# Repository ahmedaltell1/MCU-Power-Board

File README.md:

# Custom MSP430 Embedded Systems PCB

## Overview

This project is a custom-designed embedded systems PCB developed in KiCad. The board integrates a regulated power delivery stage, an MSP430 microcontroller subsystem, sensor interfaces, switch inputs, and IoT communication support into a single embedded hardware platform.

The system was designed to demonstrate practical embedded hardware development, PCB design workflow, sensor integration, power regulation, and hardware/software interfacing.

Additionally, the project incorporates an ultrasonic water-level detection system capable of monitoring liquid levels through embedded sensing and real-time signal interfacing.

---

## Features

- Custom PCB designed in KiCad
- MSP430 microcontroller integration
- Regulated power delivery subsystem
- Ultrasonic water-level detection
- Sensor interface circuitry
- Embedded switch inputs
- IoT communication module support
- Modular embedded hardware architecture
- Manufacturable PCB layout and fabrication files

---

## Hardware Components

- MSP430 microcontroller
- Voltage regulation circuitry
- Ultrasonic sensor interface
- IoT communication module
- GPIO switch interfaces
- Passive filtering and protection components

---

## Design Tools

- KiCad
- LTspice
- Embedded hardware debugging tools

---

## Repository Structure

```text
custom-msp430-pcb/
├── schematics/       # Schematic source and exported PDFs
├── pcb/              # PCB layout files and renders
├── gerbers/          # Manufacturing Gerber files

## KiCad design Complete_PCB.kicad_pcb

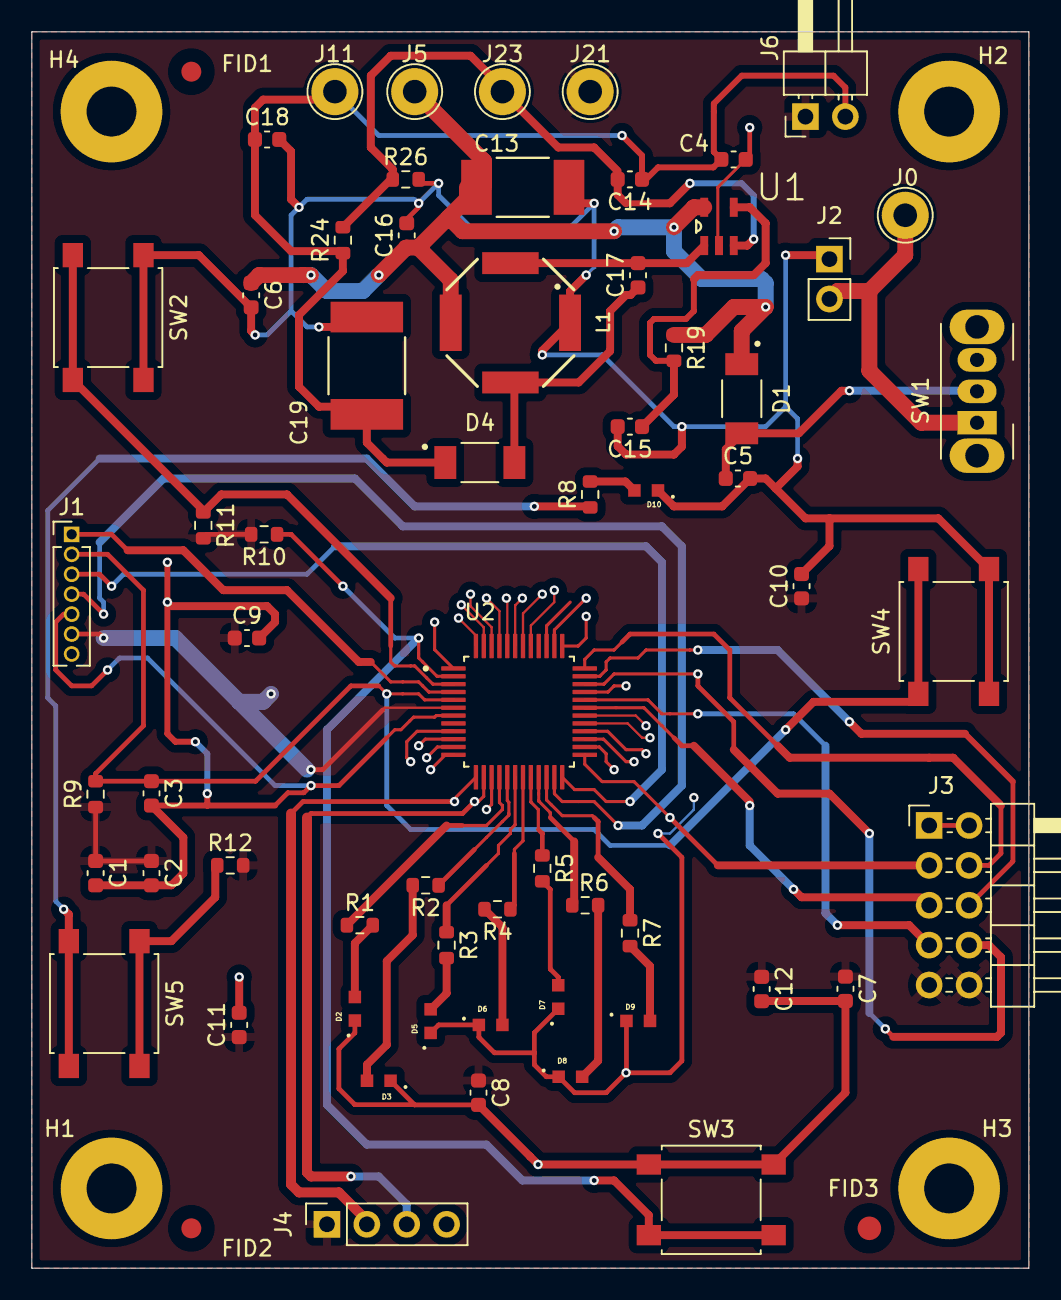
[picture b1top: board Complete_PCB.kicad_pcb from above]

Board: 2 copper layers, 63.5 x 78.7 mm, 69 parts (0 on the bottom side), 41 nets.

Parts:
C1: 0.1uF; C_0603_1608Metric
C2, C4, C5, C6, C7, C8, C9, C10, C11, C12, C18: 10uF; C_0603_1608Metric
C3: 1nF; C_0603_1608Metric
C13: 22uF; CAP_595D-C_VSS
C14, C15: 470pF; C_0603_1608Metric
C16, C17: 1uF; C_0603_1608Metric
C19: 100uF; CAP_594D-D_VSS
D1, D4: PMEG3050EP_115; DIO_PMEG3050EP_115
D2, D3, D5, D6, D7, D8, D9, D10: LTST-C190GKT; LEDM1608X80
FID1, FID2, FID3: Fiducial; Fiducial_1.5mm_Mask3mm
H1, H2, H3, H4: MountingHole_Pad; MountingHole_3.2mm_M3_Pad_TopOnly
J0, J5, J11, J21, J23: TestPoint; TestPoint_THTPad_D3.0mm_Drill1.5mm
J1: Conn_01x07_Pin; PinHeader_1x07_P1.27mm_Vertical
J2: Conn_01x02; PinSocket_1x02_P2.54mm_Vertical
J3: Conn_02x05_Odd_Even; PinHeader_2x05_P2.54mm_Horizontal
J4: Conn_01x04_Socket; PinSocket_1x04_P2.54mm_Vertical
J6: Conn_01x02_Pin; PinHeader_1x02_P2.54mm_Horizontal
L1: WE-TDC_8038
R1, R2, R3, R4, R5, R6, R7, R8: 1k; R_0603_1608Metric
R9, R10, R11, R12, R19: 10k; R_0603_1608Metric
R24: 20k; R_0603_1608Metric
R26: 12k; R_0603_1608Metric
SW1: SW_SPST; SW_Slide_SPDT_Angled_CK_OS102011MA1Q
SW2, SW3, SW4, SW5: SW_DIP_x01; SW_SPST_B3S-1000
U1: LT1935ES5TRMPBF; SOT95P280X100-5N
U2: MSP430FR2355TPT; QFP50P900X900X160-48N

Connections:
/PWR5A: C6.1, C13.1, C16.1, D1.K, J5.1, L1.3, R19.1, U1.5 (VIN)
/RAW_BAT: J0.1, J2.2, SW1.1 (A)
/Sheet2/CPU_RXDA: J3.7, U2.32 (P1.6/UCA0RXD/UCA0SOMI/TB0.1/TDI/TCLK/OA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)
/Sheet2/CPU_TXDA: J3.5, U2.31 (P1.7/UCA0TXD/UCA0SIMO/TB0.2/TDO/OA1+/A7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)
/Sheet2/Echo: J4.3, U2.14 (P4.5/UCB1CLK)
/Sheet2/IOT_BOOTA: J3.4, U2.36 (P3.6/OA3-)
/Sheet2/IOT_EN: J3.3, U2.25 (P4.1/UCA1CLK)
/Sheet2/IOT_LINK: J3.6, U2.35 (P3.7/OA3+)
/Sheet2/IOT_RUN: J3.8, U2.34 (P1.4/UCA0STE/TCK/A4)
/Sheet2/LED7: R7.1, U2.22 (P6.0/TB3.1)
/Sheet2/RST: C3.1, J1.2, R9.2, SW4.2, U2.5 (~RST/NMI/SBWTDIO)
/Sheet2/RXD: J1.3, U2.24 (P4.2/UCA1RXD/UCA1SOMI/~UCA1RXD)
/Sheet2/SW2: R11.1, SW2.2, U2.3 (P1.0/UCB0STE/SMCLK/COMP0.0/A0/VEREF+)
/Sheet2/SW3: R10.1, SW3.2, U2.2 (P1.1/UCB0CLK/ACLK/OA0O/COMP0.1/A1)
/Sheet2/TEST: J1.1, U2.4 (TEST/SBWTCK)
/Sheet2/TXD: J1.4, U2.23 (P4.3/UCA1TXD/UCA1SIMO/~UCA1TXD)
/Sheet2/Trig: J4.2, U2.13 (P4.6/UCB1SIMO/UCB1SDA)
GND: C1.2, C2.2, C3.2, C4.2, C5.2, C6.2, C7.2, C8.2, C9.2, C10.2, C11.2, C12.2, C13.2, C15.2, C16.2, C18.2, C19.2, D2.C, D3.C, D5.C, D6.C, D7.C, D8.C, D9.C, D10.C, J1.5, J2.1, J3.1, J3.2, J4.4, L1.1, R26.2, SW2.1, SW3.1, SW4.1, U1.2 (GND), U2.7 (DVSS)
unnamed: C17.1, D4.A, L1.4
unnamed: D2.A, R1.2
unnamed: D3.A, R2.2
unnamed: D5.A, R3.2
unnamed: D6.A, R4.2
unnamed: D7.A, R5.2
unnamed: D8.A, R6.2
unnamed: D9.A, R7.2
unnamed: D10.A, R8.2
unnamed: C4.1, C14.1, C18.1, C19.1, D4.K, J6.2, J11.1, R24.1
unnamed: R8.1, SW5.2
unnamed: R12.1, SW5.1
unnamed: C5.1, D1.A, SW1.2 (B)
unnamed: C14.2, J23.1, R24.2, R26.1, U1.3 (FB)
unnamed: C17.2, L1.2, U1.1 (SW)
unnamed: C15.1, R19.2, U1.4 (~SHDN)
unnamed: R6.1, U2.21 (P6.1/TB3.2)
unnamed: R5.1, U2.20 (P6.2/TB3.3)
unnamed: R4.1, U2.19 (P6.3/TB3.4)
unnamed: R3.1, U2.18 (P6.4/TB3.5)
unnamed: R2.1, U2.17 (P6.5/TB3.6)
unnamed: R1.1, U2.16 (P6.6/TB3CLK)
PWR3_3: C1.1, C2.1, C7.1, C8.1, C9.1, C10.1, C11.1, C12.1, J1.6, J3.9, J3.10, J4.1, J6.1, J21.1, R9.1, R10.2, R11.2, R12.2, U2.6 (DVCC)

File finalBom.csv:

"Reference","Qty","Value","DNP","Exclude from BOM","Exclude from Board","Footprint","Datasheet"
"C1","1","0.1uF","","","","Capacitor_SMD:C_0603_1608Metric","~"
"C2,C4,C5,C6,C7,C8,C9,C10,C11,C12,C18","11","10uF","","","","Capacitor_SMD:C_0603_1608Metric","~"
"C3","1","1nF","","","","Capacitor_SMD:C_0603_1608Metric","~"
"C13","1","22uF","","","","footprints:CAP_595D-C_VSS","~"
"C14,C15","2","470pF","","","","Capacitor_SMD:C_0603_1608Metric","~"
"C16,C17","2","1uF","","","","Capacitor_SMD:C_0603_1608Metric","~"
"C19","1","100uF","","","","footprints100uF:CAP_594D-D_VSS","~"
"D1,D4","2","PMEG3050EP_115","","","","PMEG3050EP_115:DIO_PMEG3050EP_115",""
"D2,D3,D5,D6,D7,D8,D9,D10","8","LTST-C190GKT","","","","LTST-C190GKT:LEDM1608X80",""
"FID1,FID2,FID3","3","Fiducial","","Excluded from BOM","","Fiducial:Fiducial_1.5mm_Mask3mm","~"
"H1,H2,H3,H4","4","MountingHole_Pad","","Excluded from BOM","","MountingHole:MountingHole_3.2mm_M3_Pad_TopOnly","~"
"J0,J5,J11,J21,J23","5","TestPoint","","","","TestPoint:TestPoint_THTPad_D3.0mm_Drill1.5mm","~"
"J1","1","Conn_01x07_Pin","","","","Connector_PinHeader_1.27mm:PinHeader_1x07_P1.27mm_Vertical","~"
"J2","1","Conn_01x02","","","","Connector_PinSocket_2.54mm:PinSocket_1x02_P2.54mm_Vertical","~"
"J3","1","Conn_02x05_Odd_Even","","","","Connector_PinHeader_2.54mm:PinHeader_2x05_P2.54mm_Horizontal","~"
"J4","1","Conn_01x04_Socket","","","","Connector_PinSocket_2.54mm:PinSocket_1x04_P2.54mm_Vertical","~"
"J6","1","Conn_01x02_Pin","","","","Connector_PinHeader_2.54mm:PinHeader_1x02_P2.54mm_Horizontal","~"
"L1","1","WE-TDC_8038","","","","74489440100:WE-TDC_8038",""
"R1,R2,R3,R4,R5,R6,R7,R8","8","1k","","","","Resistor_SMD:R_0603_1608Metric","~"
"R9,R10,R11,R12,R19","5","10k","","","","Resistor_SMD:R_0603_1608Metric","~"
"R24","1","20k","","","","Resistor_SMD:R_0603_1608Metric","~"
"R26","1","12k","","","","Resistor_SMD:R_0603_1608Metric","~"
"SW1","1","SW_SPST","","","","Button_Switch_THT:SW_Slide_SPDT_Angled_CK_OS102011MA1Q","~"
"SW2,SW3,SW4,SW5","4","SW_DIP_x01","","","","Button_Switch_SMD:SW_SPST_B3S-1000","~"
"U1","1","LT1935ES5TRMPBF","","","","LT1935ES5TRMPBF:SOT95P280X100-5N",""
"U2","1","MSP430FR2355TPT","","","","MSP430FR2355TPT:QFP50P900X900X160-48N",""
"U3","1","4007","","","","4007:MODULE_4007",""

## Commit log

2026-05-11 Rename 492Homework6.kicad_pcb to Complete_PCB.kicad_pcb
2026-05-11 Rename 492Homework6.kicad_prl to Kicad_Specifications.kicad_prl
2026-05-11 Rename 492Homework6.kicad_sch to Complete_PCB.kicad_sch
2026-05-11 Rename 492Homework6.kicad_pro to Complete_PCB.kicad_pro
2026-05-11 Gerber Files
2026-05-12 Updated Structure
